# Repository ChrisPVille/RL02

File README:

Folder list:
board          - KiCad project, schematics and gerbers for board
FPGA           - Xilinx ISE Project
uC             - TI CCS project and C sources for micro-controller
Reference Docs - Supporting documentation for the RL02 and related

# RL02-USB Interface Project

## Overview

The aim of this project is to create an open-source interface between the DEC RL02 and a modern computer via USB.  

## Background

The RL02 hard drive was a mainstay of DEC's packaged computer systems in the late 1970s and 1980s.  Storing 10MB of data, these drives featured removable platters, 55ms average seek times, and ~250KBps effective linear throughput.  Combined with the modular design and longevity of the product line, there are still many functioning drives and many disk packs out there.

In addition to the historical aspects, many people still operate vintage computers for fun and profit.  Setting up operating system images and transferring files can be an ordeal when they can only be moved via serial or sneakernet from a very old system to a moderately old system to a modern system.  This interface serves to obviate the need for such setups by allowing the direct interface of the RL02 with a modern computer.

## The Interface

This new interface uses an FPGA to do all drive-facing tasks such as MFM data decoding, clock recovery, drive management, data buffering, etc.  The FPGA communicates with a microcontroller, exposing its data and a command interface over SPI.  That microcontroller serves as the USB mass storage/bulk transport device for the attached PC.

### FPGA

TODO: Expand

### Microcontroller

TODO: Expand

### PCB

TODO: Expand

(C) 2015 Christopher Parish

This program is free software: you can redistribute it and/or modify
it under the terms of the GNU General Public License as published by
the Free Software Foundation, either version 3 of the License, or
(at your option) any later version.  This is subject to the
exceptions listed in the LICENSE_EXCEPTION file.

This program is distributed in the hope that it will be useful,
but WITHOUT ANY WARRANTY; without even the implied warranty of
MERCHANTABILITY or FITNESS FOR A PARTICULAR PURPOSE.  See the
GNU General Public License for more details.

You should have received a copy of the GNU General Public License
along with this program.  If not, see <http://www.gnu.org/licenses/>.

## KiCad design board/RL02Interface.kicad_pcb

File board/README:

This folder contains the KiCad (https://launchpad.net/kicad) project files, schematic symbols, and related footprints as well as generated schematics and gerber files.

I generally run the latest KiCad built from sources, so I may be using features that don't exist in the pre-built versions.

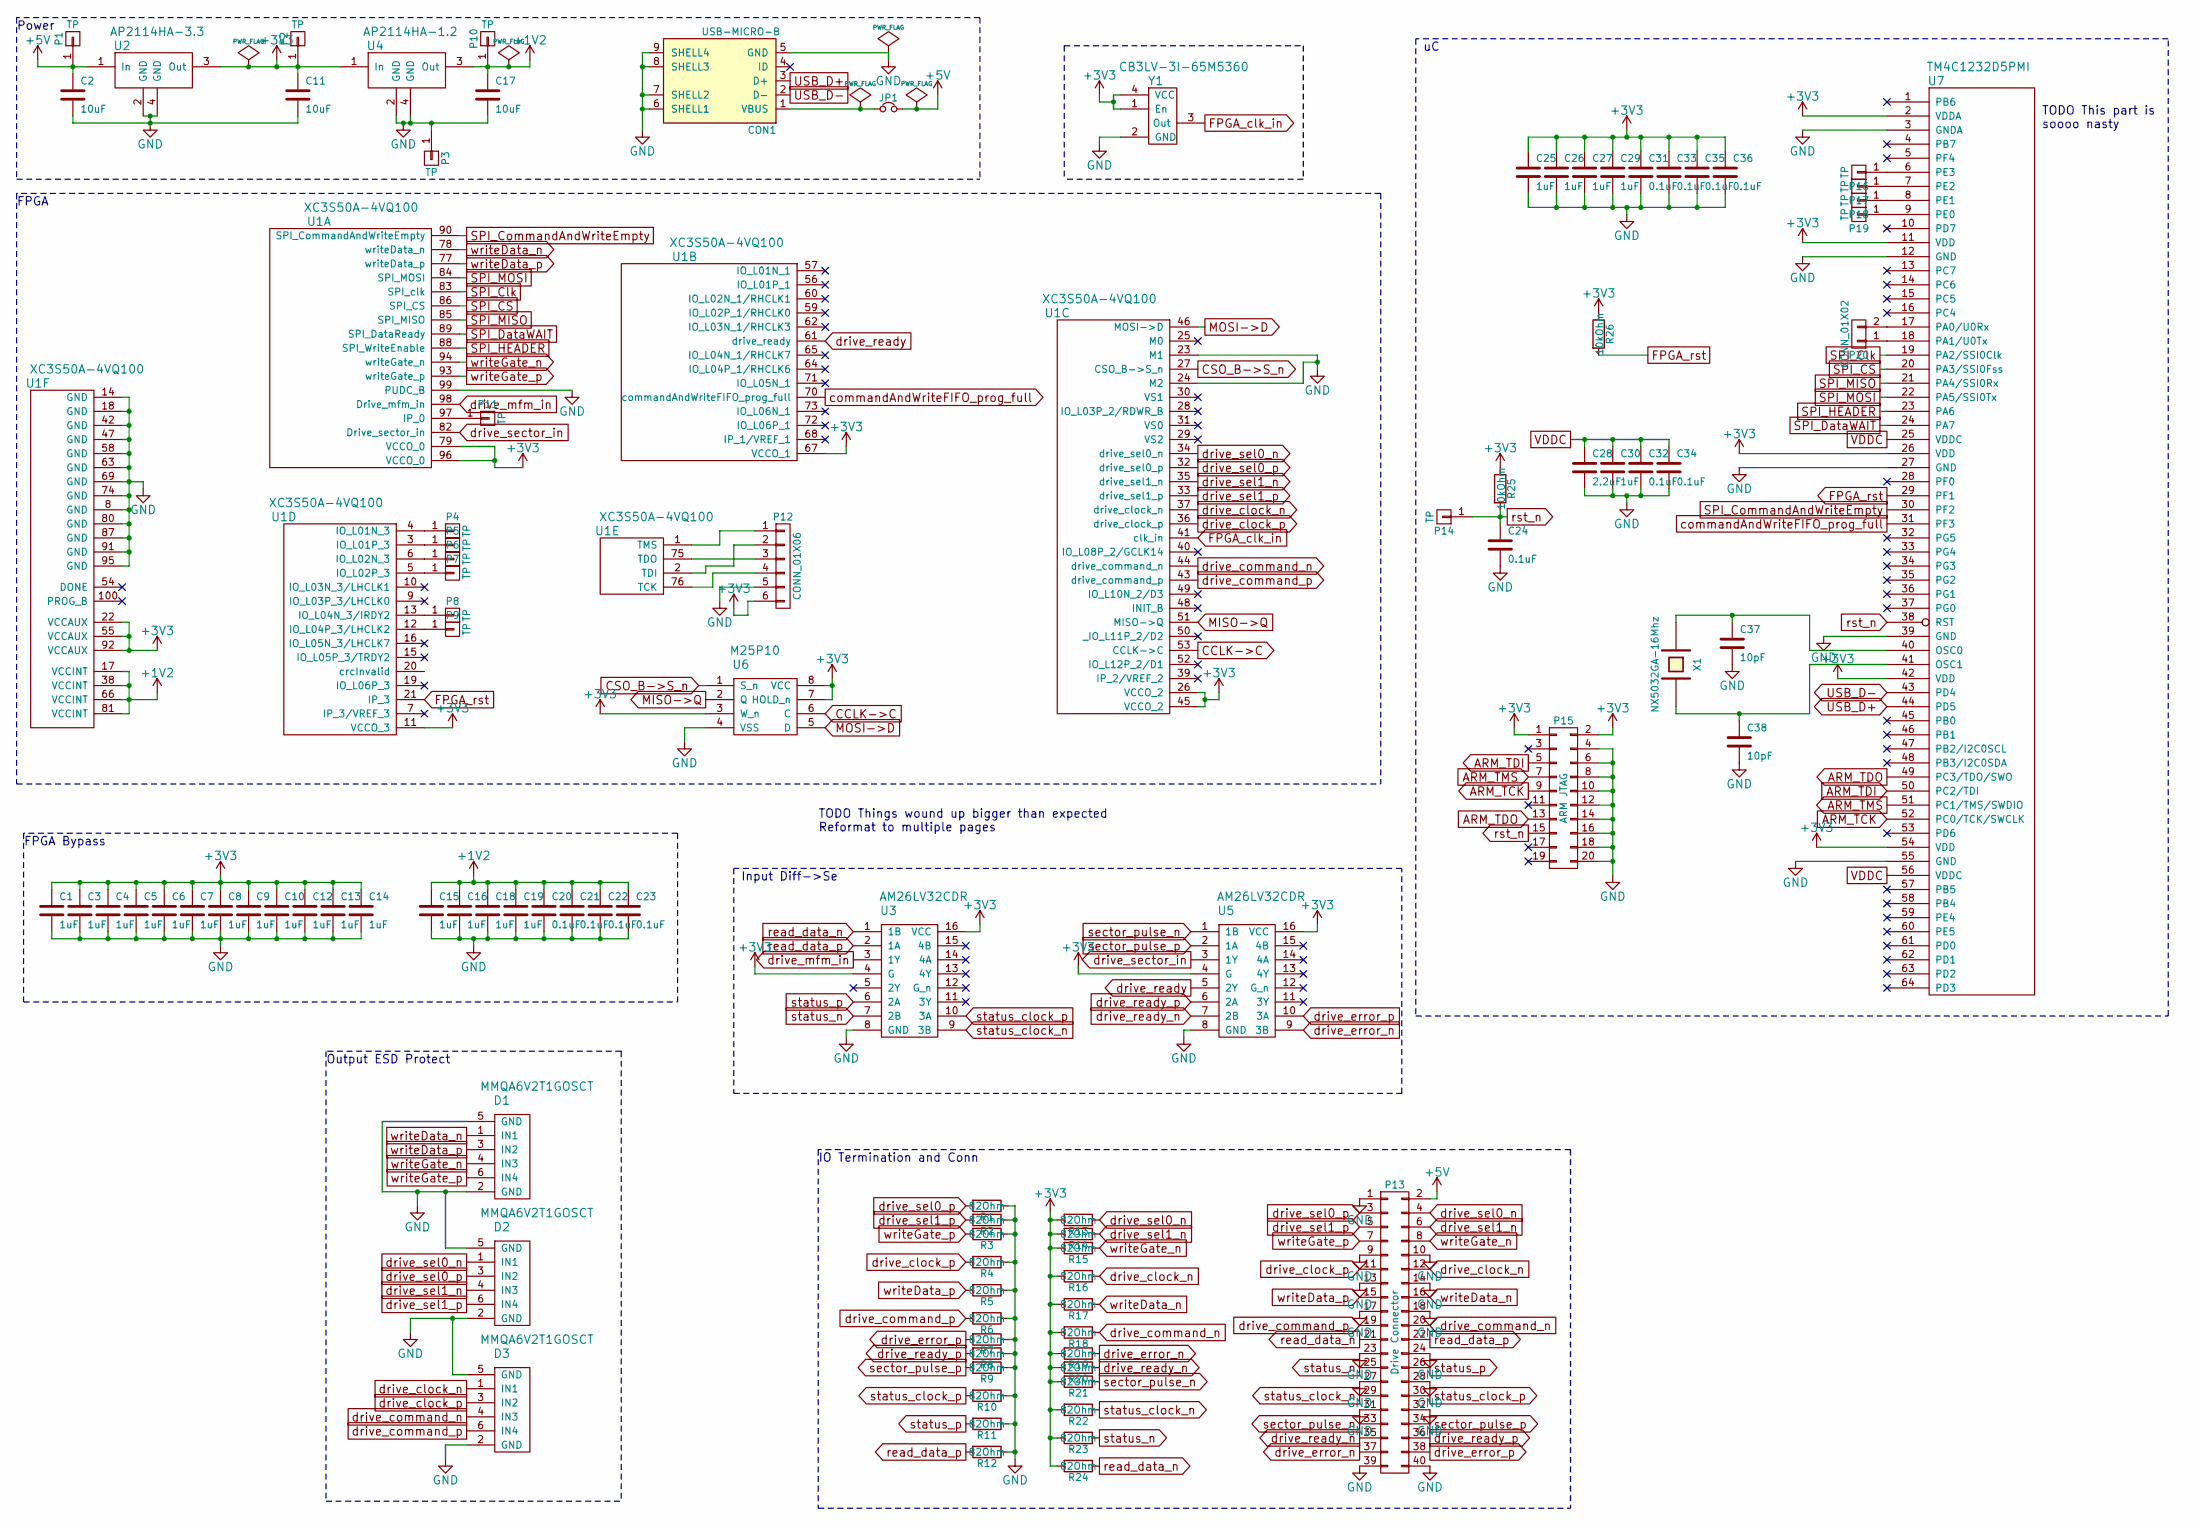
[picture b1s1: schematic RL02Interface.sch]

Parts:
C1, C3, C4, C5, C6, C7, C8, C9, C10, C12, C13, C14, C15, C16, C18, C19, C25, C26, C27, C29, C30: 1uF; C_0805
C2, C11, C17: 10uF; C_0805
C20, C21, C22, C23, C24, C31, C32, C33, C34, C35, C36: 0.1uF; C_0805
C28: 2.2uF; C_0805
C37, C38: 10pF; C_0805
CON1: USB-MICRO-B; MicroUSB-B
D1, D2, D3: MMQA6V2T1GOSCT; SOT-23-6
JP1: Jumper_NC_Small; Pin_Header_Straight_1x02
P1, P2, P3, P4, P5, P6, P7, P8, P9, P10, P11, P14, P16, P17, P18, P19: TP
P12: CONN_01X06; Pin_Header_Straight_1x06
P13: Drive Connector; Pin_Header_Straight_2x20
P15: ARM JTAG; Pin_Header_Straight_2x10
P20: CONN_01X02; Pin_Header_Straight_1x02
R1, R2, R3, R4, R5, R6, R7, R8, R9, R10, R11, R12, R13, R14, R15, R16, R17, R18, R19, R20, R21, R22, R23, R24: 82Ohm; R_0805
R25, R26: 10kOhm; R_0805
U1: XC3S50A-4VQ100; TQFP-100_14x14mm_Pitch0.5mm
U2: AP2114HA-3.3; SOT-223
U3, U5: AM26LV32CDR; SOIC-16_3.9x9.9mm_Pitch1.27mm
U4: AP2114HA-1.2; SOT-223
U6: M25P10; SOIC-8_3.9x4.9mm_Pitch1.27mm
U7: TM4C1232D5PMI; TQFP-64_10x10mm_Pitch0.5mm
X1: NX5032GA-16Mhz; C_1210_HandSoldering
Y1: CB3LV-3I-65M5360; CTSCrystal

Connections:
+1V2: C15.1, C16.1, C17.1, C18.1, C19.1, C20.1, C21.1, C22.1, C23.1, P10.1, U1.17 (VCCINT), U1.38 (VCCINT), U1.66 (VCCINT), U1.81 (VCCINT), U4.3 (Out); also elsewhere on the board
+3V3: C1.1, C3.1, C4.1, C5.1, C6.1, C7.1, C8.1, C9.1, C10.1, C11.1, C12.1, C13.1, C14.1, C25.1, C26.1, C27.1, C29.1, C31.1, C33.1, C35.1, C36.1, P2.1, P12.6, P15.1, P15.2, R13.2, R14.2, R15.2, R16.2, R17.2, R18.2, R19.2, R20.2, R21.2, R22.2, R23.2, R24.2, R25.1, R26.1, U1.11 (VCCO_3), U1.22 (VCCAUX), U1.26 (VCCO_2), U1.45 (VCCO_2), U1.55 (VCCAUX), U1.67 (VCCO_1), U1.79 (VCCO_0), U1.92 (VCCAUX), U1.96 (VCCO_0), U2.3 (Out), U3.4 (G), U3.16 (VCC), U4.1 (In), U5.4 (G), U5.16 (VCC), U6.3 (W_n), U6.7 (HOLD_n), U6.8 (VCC), U7.2 (VDDA), U7.11 (VDD), U7.26 (VDD), U7.42 (VDD), U7.54 (VDD), Y1.1 (En), Y1.4 (VCC); also elsewhere on the board
+5V: C2.1, JP1.2, P1.1, P13.2, U2.1 (In); also elsewhere on the board
ARM_TCK: P15.9, U7.52 (PC0/TCK/SWCLK)
ARM_TDI: P15.5, U7.50 (PC2/TDI)
ARM_TDO: P15.13, U7.49 (PC3/TDO/SWO)
ARM_TMS: P15.7, U7.51 (PC1/TMS/SWDIO)
CCLK->C: U1.53 (CCLK->C), U6.6 (C)
CSO_B->S_n: U1.27 (CSO_B->S_n), U6.1 (S_n)
FPGA_clk_in: U1.41 (clk_in), Y1.3 (Out)
FPGA_rst: R26.2, U1.21 (IP_3), U7.29 (PF1)
GND: C1.2, C2.2, C3.2, C4.2, C5.2, C6.2, C7.2, C8.2, C9.2, C10.2, C11.2, C12.2, C13.2, C14.2, C15.2, C16.2, C17.2, C18.2, C19.2, C20.2, C21.2, C22.2, C23.2, C24.2, C25.2, C26.2, C27.2, C28.2, C29.2, C30.2, C31.2, C32.2, C33.2, C34.2, C35.2, C36.2, C37.2, C38.2, CON1.5 (GND), CON1.6 (SHELL1), CON1.7 (SHELL2), CON1.8 (SHELL3), CON1.9 (SHELL4), CON1.PAD, D1.2 (GND), D1.5 (GND), D2.2 (GND), D2.5 (GND), D3.2 (GND), D3.5 (GND), P3.1, P12.5, P13.1, P13.9, P13.10, P13.13, P13.14, P13.17, P13.18, P13.23, P13.24, P13.27, P13.28, P13.31, P13.32, P13.39, P13.40, P15.4, P15.6, P15.8, P15.10, P15.12, P15.14, P15.16, P15.18, P15.20, R1.1, R2.1, R3.1, R4.1, R5.1, R6.1, R7.1, R8.1, R9.1, R10.1, R11.1, R12.1, U1.8 (GND), U1.14 (GND), U1.18 (GND), U1.23 (M1), U1.24 (M2), U1.42 (GND), U1.47 (GND), U1.58 (GND), U1.63 (GND), U1.69 (GND), U1.74 (GND), U1.80 (GND), U1.87 (GND), U1.91 (GND), U1.95 (GND), U1.99 (PUDC_B), U2.2 (GND), U2.4 (GND), U3.8 (GND), U4.2 (GND), U4.4 (GND), U5.8 (GND), U6.4 (VSS), U7.3 (GNDA), U7.12 (GND), U7.27 (GND), U7.39 (GND), U7.55 (GND), Y1.2 (GND); also elsewhere on the board
MISO->Q: U1.51 (MISO->Q), U6.2 (Q)
MOSI->D: U1.46 (MOSI->D), U6.5 (D)
unnamed: C37.1, U7.40 (OSC0), X1.1
unnamed: C38.1, U7.41 (OSC1), X1.2
unnamed: CON1.1 (VBUS), JP1.1
unnamed: P4.1, U1.4 (IO_L01N_3)
unnamed: P5.1, U1.3 (IO_L01P_3)
unnamed: P6.1, U1.6 (IO_L02N_3)
unnamed: P7.1, U1.5 (IO_L02P_3)
unnamed: P8.1, U1.13 (IO_L04N_3/IRDY2)
unnamed: P9.1, U1.12 (IO_L04P_3/LHCLK2)
unnamed: P11.1, U1.97 (IP_0)
unnamed: P12.1, U1.1 (TMS)
unnamed: P12.2, U1.2 (TDI)
unnamed: P12.3, U1.75 (TDO)
unnamed: P12.4, U1.76 (TCK)
unnamed: P16.1, U7.6 (PE3)
unnamed: P17.1, U7.7 (PE2)
unnamed: P18.1, U7.8 (PE1)
unnamed: P19.1, U7.9 (PE0)
unnamed: P20.1, U7.18 (PA1/U0Tx)
unnamed: P20.2, U7.17 (PA0/U0Rx)
SPI_CS: U1.86 (SPI_CS), U7.20 (PA3/SSI0Fss)
SPI_Clk: U1.83 (SPI_clk), U7.19 (PA2/SSI0Clk)
SPI_CommandAndWriteEmpty: U1.90 (SPI_CommandAndWriteEmpty), U7.30 (PF2)
SPI_DataWAIT: U1.89 (SPI_DataReady), U7.24 (PA7)
SPI_HEADER: U1.88 (SPI_WriteEnable), U7.23 (PA6)
SPI_MISO: U1.85 (SPI_MISO), U7.21 (PA4/SSI0Rx)
SPI_MOSI: U1.84 (SPI_MOSI), U7.22 (PA5/SSI0Tx)
USB_D+: CON1.3 (D+), U7.44 (PD5)
USB_D-: CON1.2 (D-), U7.43 (PD4)
VDDC: C28.1, C30.1, C32.1, C34.1, U7.25 (VDDC), U7.56 (VDDC)
commandAndWriteFIFO_prog_full: U1.70 (commandAndWriteFIFO_prog_full), U7.31 (PF3)
drive_clock_n: D3.1 (IN1), P13.12, R16.1, U1.37 (drive_clock_n)
drive_clock_p: D3.3 (IN2), P13.11, R4.2, U1.36 (drive_clock_p)
drive_command_n: D3.4 (IN3), P13.20, R18.1, U1.44 (drive_command_n)
drive_command_p: D3.6 (IN4), P13.19, R6.2, U1.43 (drive_command_p)
drive_error_n: P13.37, R19.1, U5.9 (3B)
drive_error_p: P13.38, R7.2, U5.10 (3A)
drive_mfm_in: U1.98 (Drive_mfm_in), U3.3 (1Y)
drive_ready: U1.61 (drive_ready), U5.5 (2Y)
drive_ready_n: P13.35, R20.1, U5.7 (2B)
drive_ready_p: P13.36, R8.2, U5.6 (2A)
drive_sector_in: U1.82 (Drive_sector_in), U5.3 (1Y)
drive_sel0_n: D2.1 (IN1), P13.4, R13.1, U1.34 (drive_sel0_n)
drive_sel0_p: D2.3 (IN2), P13.3, R1.2, U1.32 (drive_sel0_p)
drive_sel1_n: D2.4 (IN3), P13.6, R14.1, U1.35 (drive_sel1_n)
drive_sel1_p: D2.6 (IN4), P13.5, R2.2, U1.33 (drive_sel1_p)
read_data_n: P13.21, R24.1, U3.1 (1B)
read_data_p: P13.22, R12.2, U3.2 (1A)
rst_n: C24.1, P14.1, P15.15, R25.2, U7.38 (RST); also elsewhere on the board
sector_pulse_n: P13.33, R21.1, U5.1 (1B)
sector_pulse_p: P13.34, R9.2, U5.2 (1A)
status_clock_n: P13.29, R22.1, U3.9 (3B)
status_clock_p: P13.30, R10.2, U3.10 (3A)
status_n: P13.25, R23.1, U3.7 (2B)
status_p: P13.26, R11.2, U3.6 (2A)
writeData_n: D1.1 (IN1), P13.16, R17.1, U1.78 (writeData_n)
writeData_p: D1.3 (IN2), P13.15, R5.2, U1.77 (writeData_p)
writeGate_n: D1.4 (IN3), P13.8, R15.1, U1.94 (writeGate_n)
writeGate_p: D1.6 (IN4), P13.7, R3.2, U1.93 (writeGate_p)

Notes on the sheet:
TODO This part is soooo nasty
TODO Things wound up bigger than expected Reformat to multiple pages
FPGA
Power
FPGA Bypass
Output ESD Protect
IO Termination and Conn
Input Diff->Se

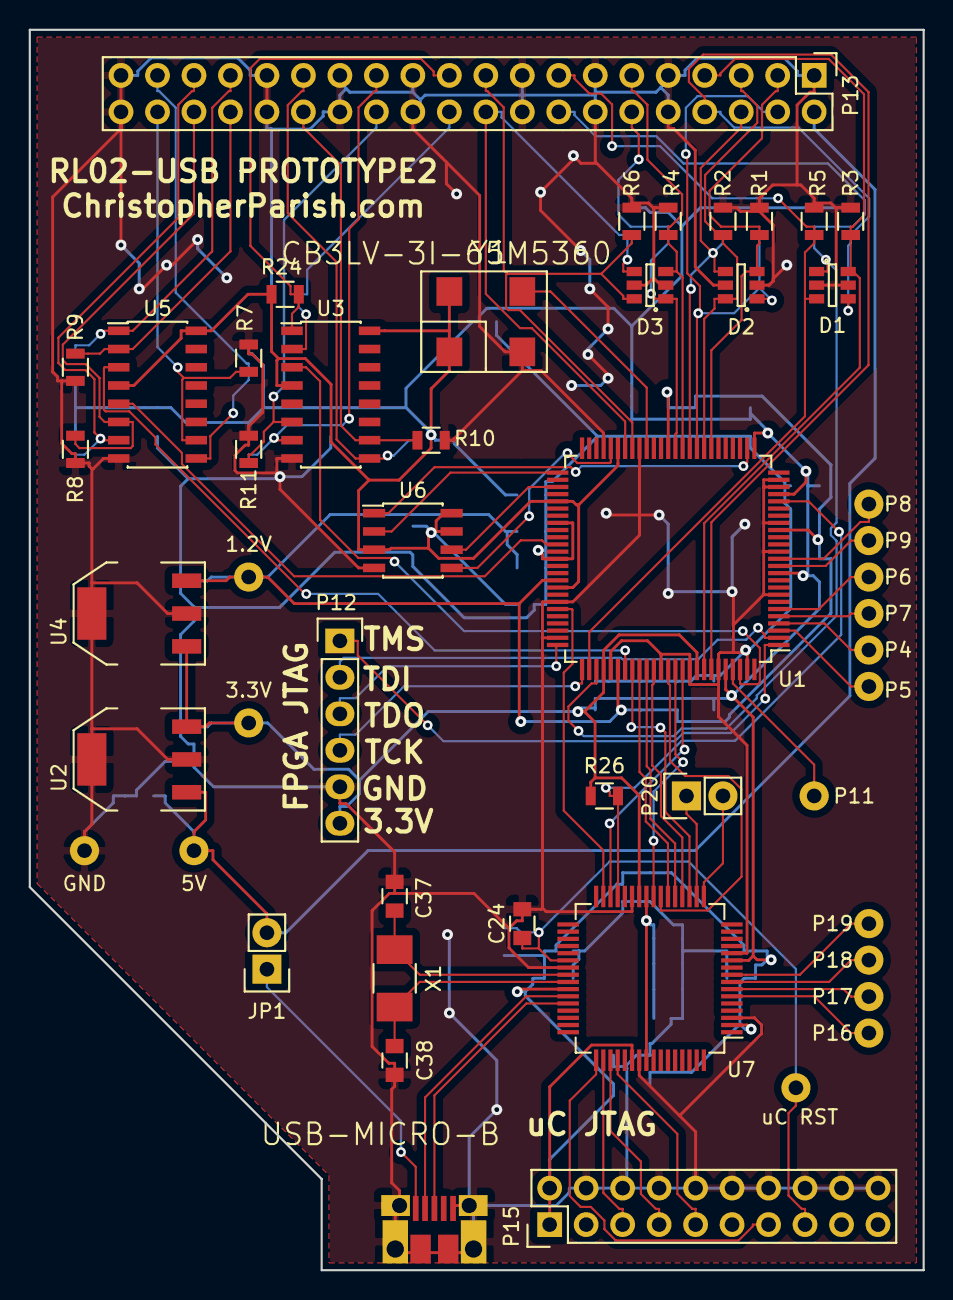
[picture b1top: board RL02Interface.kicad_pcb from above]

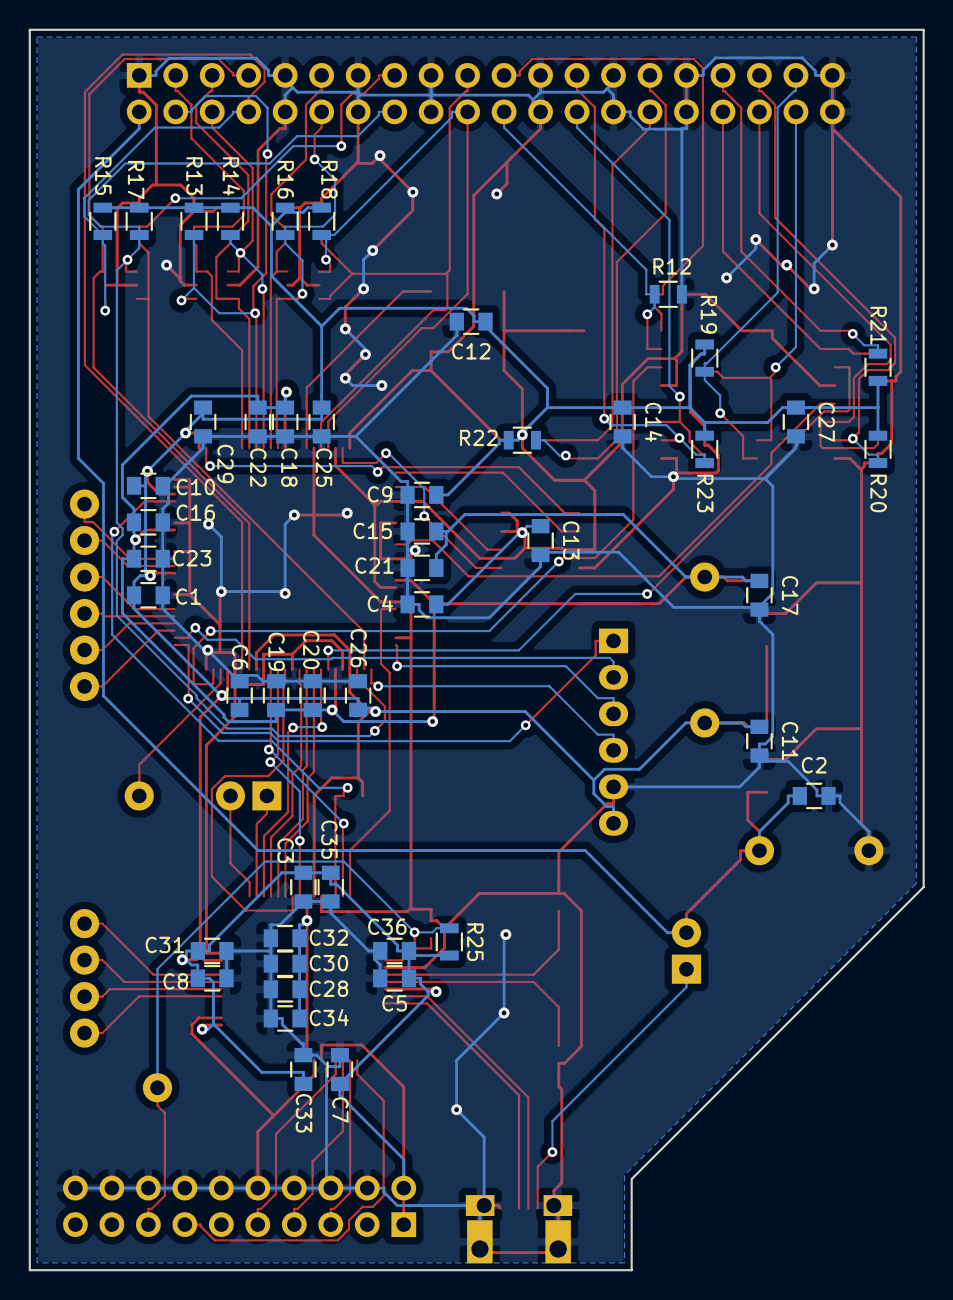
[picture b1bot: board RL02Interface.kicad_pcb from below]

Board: 2 copper layers, 62.2 x 86.4 mm, 98 parts (48 on the bottom side), 73 nets.

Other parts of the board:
1.2V, 3.3V, 5V: TP
GND: TP
uC RST: TP

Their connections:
+1V2: 1.2V.1; also elsewhere on the board
+3V3: 3.3V.1; also elsewhere on the board
+5V: 5V.1; also elsewhere on the board
GND: GND.1; also elsewhere on the board
rst_n: uC RST.1; also elsewhere on the board

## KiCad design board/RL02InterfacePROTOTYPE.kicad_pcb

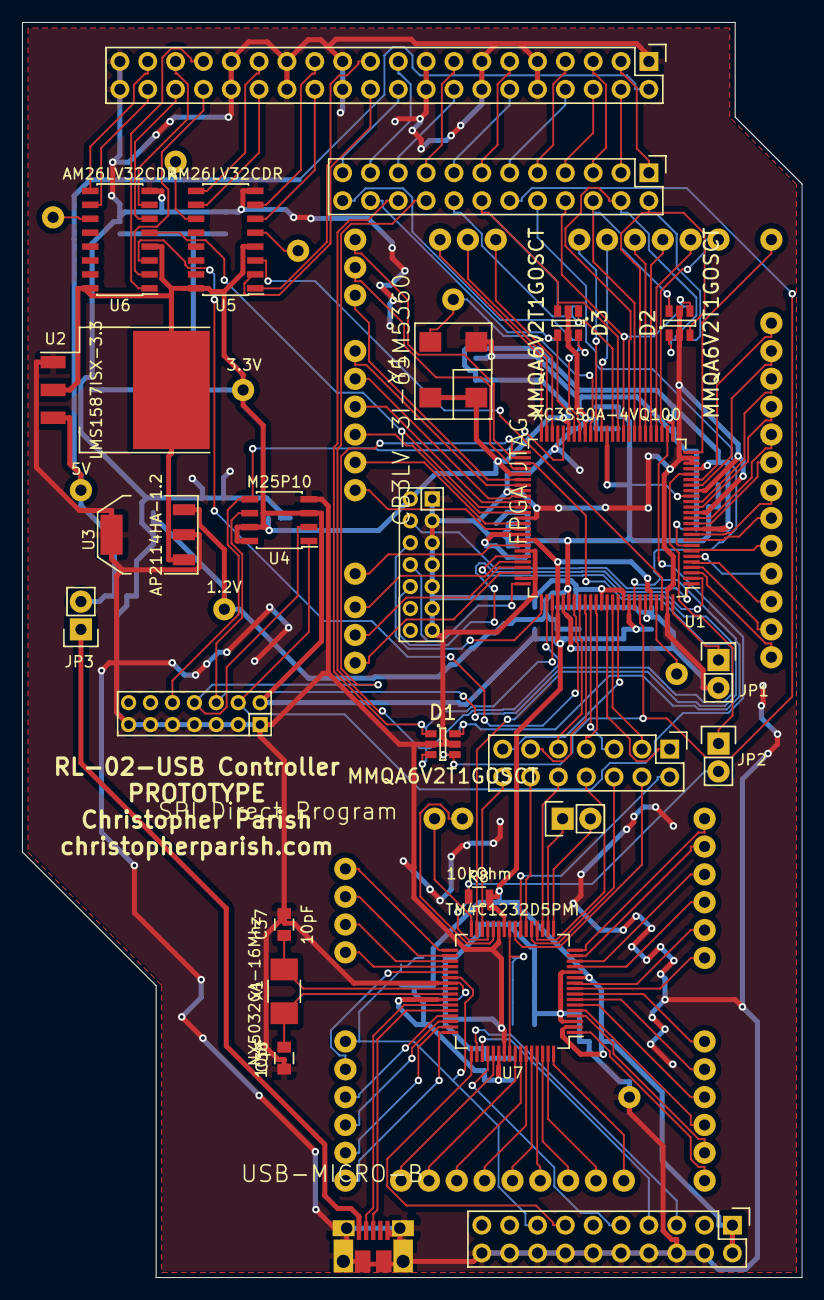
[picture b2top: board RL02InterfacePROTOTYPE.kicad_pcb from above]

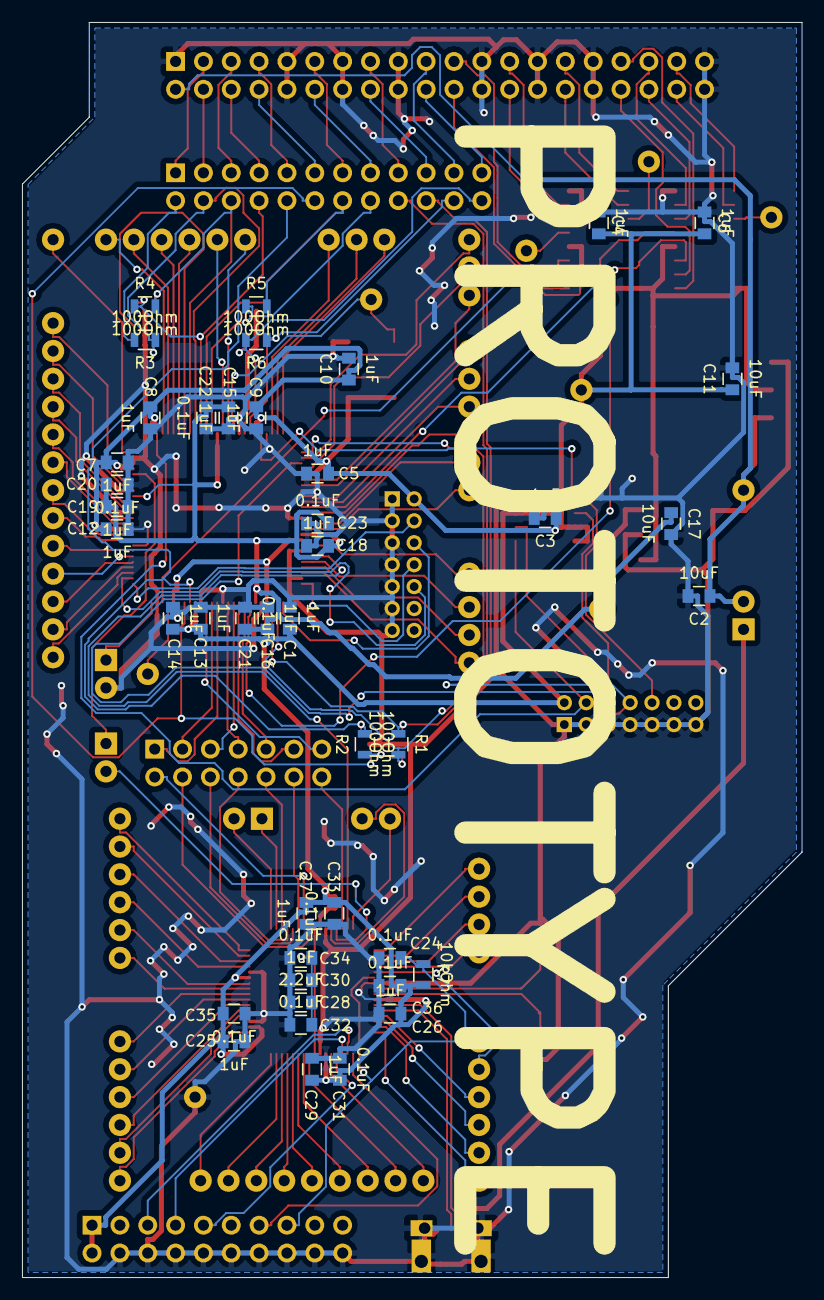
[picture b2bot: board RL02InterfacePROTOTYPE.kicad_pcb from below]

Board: 2 copper layers, 71.1 x 114.5 mm, 147 parts (43 on the bottom side), 155 nets.

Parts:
1.2V, 3.3V, 5V: TP
C1, C3, C4, C5, C6, C7, C8, C9, C10, C12, C13, C14, C15, C16, C18, C19, C25, C26, C27, C29, C30: 1uF; C_0805
C2, C11, C17: 10uF; C_0805
C20, C21, C22, C23, C24, C31, C32, C33, C34, C35, C36: 0.1uF; C_0805
C28: 2.2uF; C_0805
C37, C38: 10pF; C_0805
CON1: USB-MICRO-B; MicroUSB-B
D1, D2, D3: MMQA6V2T1GOSCT; SOT-23-6
JP1: SPI_PROGRAM; Pin_Header_Straight_1x02
JP2, JP3: JUMPER; Pin_Header_Straight_1x02
P2, P4, P5, P6, P7, P8, P9, P10, P11, P12, P13, P14, P15, P16, P17, P19, P23, P24, P25, P26, P27, P28, P29, P30, P31, P32, P33, P34, P35, P36, P37, P38, P39, P40, P41, P42, P43, P44, P45, P46, P47, P50, P52, P53, P54, P55, P56, P57, P58, P59, P60, P61, P62, P63, P65, P66, P67, P68, P69, P70, P71, P72, P73, P74, P75, P76, P77, P78, P79, P80, P81, P82, P83, P84, P85: TP
P20: SPI Debug; Pin_Header_Straight_2x07
P21: FPGA JTAG; 2x7_2.00mm_header
P22: SPI Direct Program; 2x7_2.00mm_header
P48: Data To Drive Disconnect; Pin_Header_Straight_2x12
P49: Drive Connector; Pin_Header_Straight_2x20
P51: ARM JTAG; Pin_Header_Straight_2x10
P64: CONN_01X02; Pin_Header_Straight_1x02
R1, R2, R3, R4, R5, R6: 100Ohm; R_0805
R7, R8: 10kOhm; R_0805
U1: XC3S50A-4VQ100; TQFP-100_14x14mm_Pitch0.5mm
U2: LMS1587ISX-3.3; TO-263
U3: AP2114HA-1.2; SOT-223
U4: M25P10; SOIC-8_3.9x4.9mm_Pitch1.27mm
U5, U6: AM26LV32CDR; SOIC-16_3.9x9.9mm_Pitch1.27mm
U7: TM4C1232D5PMI; TQFP-64_10x10mm_Pitch0.5mm
X1: NX5032GA-16Mhz; C_1210_HandSoldering
Y1: CB3LV-3I-65M5360; CTSCrystal

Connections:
+1V2: 1.2V.1, C15.1, C16.1, C17.1, C18.1, C19.1, C20.1, C21.1, C22.1, C23.1, U1.17, U1.38, U1.66, U1.81, U3.3
+3V3: 3.3V.1, C1.1, C3.1, C4.1, C5.1, C6.1, C7.1, C8.1, C9.1, C10.1, C11.1, C12.1, C13.1, C14.1, C25.1, C26.1, C27.1, C29.1, C31.1, C33.1, C35.1, C36.1, P21.2, P22.2, P51.1, P51.2, R7.1, R8.1, U1.11, U1.22, U1.26, U1.45, U1.55, U1.67, U1.79, U1.92, U1.96, U2.2, U2.PAD, U3.1, U4.3, U4.7, U4.8, U5.4, U5.16, U6.4, U6.16, U7.2, U7.11, U7.26, U7.42, U7.54, Y1.1, Y1.4
+5V: 5V.1, C2.1, JP3.2, P49.2, U2.3
ARM_TCK: P51.9, U7.52
ARM_TDI: P51.5, U7.50
ARM_TDO: P51.13, U7.49
ARM_TMS: P51.7, U7.51
CCLK->C: P22.6, U1.53, U4.6
CSO_B->S_n: P22.4, U1.27, U4.1
FPGA_clk_in: P66.1, U1.41, Y1.3
FPGA_rst: JP2.2, R8.2, U7.29
GND: C1.2, C2.2, C3.2, C4.2, C5.2, C6.2, C7.2, C8.2, C9.2, C10.2, C11.2, C12.2, C13.2, C14.2, C15.2, C16.2, C17.2, C18.2, C19.2, C20.2, C21.2, C22.2, C23.2, C24.2, C25.2, C26.2, C27.2, C28.2, C29.2, C30.2, C31.2, C32.2, C33.2, C34.2, C35.2, C36.2, C37.2, C38.2, CON1.5, CON1.PAD, D1.2, D1.5, D2.2, D2.5, D3.2, D3.5, JP1.2, P4.1, P21.1, P21.3, P21.5, P21.7, P21.9, P21.11, P21.13, P22.1, P22.3, P22.5, P22.7, P22.9, P22.11, P22.13, P49.1, P49.9, P49.10, P49.13, P49.14, P49.17, P49.18, P49.23, P49.24, P49.27, P49.28, P49.31, P49.32, P49.39, P49.40, P51.4, P51.6, P51.8, P51.10, P51.12, P51.14, P51.16, P51.18, P51.20, U1.8, U1.14, U1.18, U1.23, U1.24, U1.42, U1.47, U1.58, U1.63, U1.69, U1.74, U1.80, U1.87, U1.91, U1.95, U1.99, U2.1, U3.2, U3.4, U4.4, U5.8, U6.8, U7.3, U7.12, U7.27, U7.39, U7.55, Y1.2
MISO->Q: P22.8, U1.51, U4.2
MOSI->D: P22.10, U1.46, U4.5
unnamed: C37.1, U7.40, X1.1
unnamed: C38.1, U7.41, X1.2
unnamed: CON1.1, JP3.1
unnamed: JP1.1, U1.100
unnamed: JP2.1, U1.21
unnamed: P2.1, U1.54
unnamed: P5.1, U1.4
unnamed: P6.1, U1.3
unnamed: P7.1, U1.6
unnamed: P8.1, U1.5
unnamed: P9.1, U1.10
unnamed: P10.1, U1.9
unnamed: P11.1, U1.13
unnamed: P12.1, U1.12
unnamed: P13.1, U1.16
unnamed: P14.1, U1.15
unnamed: P15.1, U1.20
unnamed: P16.1, U1.19
unnamed: P17.1, U1.7
unnamed: P19.1, U1.97
unnamed: P20.1, U1.88
unnamed: P20.3, U1.89
unnamed: P20.5, U1.85
unnamed: P20.7, U1.86
unnamed: P20.9, U1.83
unnamed: P20.11, U1.84
unnamed: P20.13, U1.90
unnamed: P21.4, U1.1
unnamed: P21.6, U1.76
unnamed: P21.8, U1.75
unnamed: P21.10, U1.2
unnamed: P23.1, U1.57
unnamed: P24.1, U1.56
unnamed: P25.1, U1.60
unnamed: P26.1, U1.59
unnamed: P27.1, U1.62
unnamed: P28.1, U1.65
unnamed: P29.1, U1.64
unnamed: P30.1, U1.71
unnamed: P31.1, U1.73
unnamed: P32.1, U1.72
unnamed: P33.1, U1.68
unnamed: P34.1, U1.25
unnamed: P35.1, U1.30
unnamed: P36.1, U1.28
unnamed: P37.1, U1.31
unnamed: P38.1, U1.29
unnamed: P39.1, U1.40
unnamed: P40.1, U1.49
unnamed: P41.1, U1.48
unnamed: P42.1, U1.50
unnamed: P43.1, U1.52
unnamed: P44.1, U1.39
unnamed: P45.1, U5.5
unnamed: P46.1, U5.11
unnamed: P47.1, U6.11
unnamed: P48.1, P49.3
unnamed: P48.3, P49.4
unnamed: P48.5, P49.5
unnamed: P48.7, P49.6
unnamed: P48.9, P49.7
unnamed: P48.11, P49.8
unnamed: P48.13, P49.11
unnamed: P48.15, P49.12
unnamed: P48.17, P49.15
unnamed: P48.19, P49.16
unnamed: P48.21, P49.19
unnamed: P48.23, P49.20
unnamed: P52.1, U7.1
unnamed: P53.1, U7.4
unnamed: P54.1, U7.5
unnamed: P55.1, U7.6
unnamed: P56.1, U7.7
unnamed: P57.1, U7.8
unnamed: P58.1, U7.9
unnamed: P59.1, U7.10
unnamed: P60.1, U7.13
unnamed: P61.1, U7.14
unnamed: P62.1, U7.15
unnamed: P63.1, U7.16
unnamed: P64.1, U7.18
unnamed: P64.2, U7.17
unnamed: P65.1, U7.28
unnamed: P67.1, U7.32
unnamed: P68.1, U7.33
unnamed: P69.1, U7.34
unnamed: P70.1, U7.35
unnamed: P71.1, U7.36
unnamed: P72.1, U7.37
unnamed: P73.1, U7.45
unnamed: P74.1, U7.46
unnamed: P75.1, U7.47
unnamed: P76.1, U7.48
unnamed: P77.1, U7.53
unnamed: P78.1, U7.57
unnamed: P79.1, U7.58
unnamed: P80.1, U7.59
unnamed: P81.1, U7.60
unnamed: P82.1, U7.61
unnamed: P83.1, U7.62
unnamed: P84.1, U7.63
unnamed: P85.1, U7.64
SPI_CS: P20.8, U7.20
SPI_Clk: P20.10, U7.19
SPI_CommandAndWriteEmpty: P20.14, U7.30
SPI_DataReady: P20.4, U7.24
SPI_MISO: P20.6, U7.21
SPI_MOSI: P20.12, U7.22
SPI_WriteEnable: P20.2, U7.23
USB_D+: CON1.3, U7.44
USB_D-: CON1.2, U7.43
VDDC: C28.1, C30.1, C32.1, C34.1, U7.25, U7.56
commandAndWriteFIFO_prog_full: U1.70, U7.31
drive_clock_n: D3.1, P48.16, R5.1, U1.37
drive_clock_p: D3.3, P48.14, R5.2, U1.36
drive_command_n: D3.4, P48.22, R6.1, U1.44
drive_command_p: D3.6, P48.24, R6.2, U1.43
drive_error_n: P49.37, U6.9
drive_error_p: P49.38, U6.10
drive_mfm_in: U1.98, U5.3
drive_ready: U1.61, U6.5
drive_ready_n: P49.35, U6.7
drive_ready_p: P49.36, U6.6
drive_sector_in: U1.82, U6.3
drive_sel0_n: D2.1, P48.4, R3.1, U1.34
drive_sel0_p: D2.3, P48.2, R3.2, U1.32
drive_sel1_n: D2.4, P48.8, R4.1, U1.35
drive_sel1_p: D2.6, P48.6, R4.2, U1.33
read_data_n: P49.21, U5.1
read_data_p: P49.22, U5.2
rst_n: C24.1, P50.1, P51.15, R7.2, U7.38
sector_pulse_n: P49.33, U6.1
sector_pulse_p: P49.34, U6.2
status_clock_n: P49.29, U5.9
status_clock_p: P49.30, U5.10
status_n: P49.25, U5.7
status_p: P49.26, U5.6
writeData_n: D1.1, P48.20, R1.1, U1.78
writeData_p: D1.3, P48.18, R1.2, U1.77
writeGate_n: D1.4, P48.12, R2.1, U1.94
writeGate_p: D1.6, P48.10, R2.2, U1.93

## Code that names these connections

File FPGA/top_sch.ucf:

//SPI Boot mode pins
CONFIG PROHIBIT = P23;
CONFIG PROHIBIT = P24;
CONFIG PROHIBIT = P25;

//SPI Variant Select Pins
CONFIG PROHIBIT = P29;
CONFIG PROHIBIT = P30;
CONFIG PROHIBIT = P31;

//PUDC_B Pull up config
CONFIG PROHIBIT = P99;

//MISO/DIN -> Q
CONFIG PROHIBIT = P51;
//CSO_B -> S_n
CONFIG PROHIBIT = P27;
//CCLK -> C
CONFIG PROHIBIT = P53;
//MOSI -> D
CONFIG PROHIBIT = P46;

//INIT_B Init done
CONFIG PROHIBIT = P48;


# Specifies the minimum (worst-case) Vccint voltage for improved timing analysis
VOLTAGE  = 1.18;

# Specifies the Vccaux voltage (Spartan-3A/6)
CONFIG VCCAUX  = 3.3;
			
NET "clk_in" TNM_NET = "clk_in";
TIMESPEC TS_clk_in = PERIOD "clk_in" 65.536 MHz HIGH 50 % INPUT_JITTER 3 ps;


NET "SPI_CommandAndWriteEmpty" LOC = P90;
NET "SPI_DataWAIT" LOC = P89;
NET "SPI_MOSI" LOC = P84;
NET "SPI_CurWordIsHeader" LOC = P88;
NET "SPI_MISO" LOC = P85;
NET "SPI_CS" LOC = P86;
NET "SPI_clk" LOC = P83;

#pin2ucf - Sun Mar 08 22:31:16 2015
#The following constraints were newly added
NET "writeData_n" LOC = P78;
NET "writeData_p" LOC = P77;
NET "drive_command_n" LOC = P44;
NET "writeGate_n" LOC = P94;
NET "writeGate_p" LOC = P93;
NET "drive_command_p" LOC = P43;
NET "drive_clock_n" LOC = P37;
NET "drive_clock_p" LOC = P36;
NET "Drive_sector_in" LOC = P82;
NET "clk_in" LOC = P41;
NET "crcInvalid" LOC = P20;
NET "drive_ready" LOC = P61;
NET "drive_sel0_n" LOC = P34;
NET "drive_sel0_p" LOC = P32;
NET "commandAndWriteFIFO_prog_full" LOC = P70;
NET "drive_sel1_n" LOC = P35;
NET "drive_sel1_p" LOC = P33;
NET "Drive_mfm_in" LOC = P98;
NET "rst_in" LOC = P21;


# PlanAhead Generated IO constraints 

NET "clk_in" IOSTANDARD = LVCMOS33;
NET "commandAndWriteFIFO_prog_full" IOSTANDARD = LVCMOS33;
NET "crcInvalid" IOSTANDARD = LVCMOS33;
NET "Drive_mfm_in" IOSTANDARD = LVCMOS33;
NET "drive_ready" IOSTANDARD = LVCMOS33;
NET "Drive_sector_in" IOSTANDARD = LVCMOS33;
NET "rst_in" IOSTANDARD = LVCMOS33;
NET "SPI_clk" IOSTANDARD = LVCMOS33;
NET "SPI_CommandAndWriteEmpty" IOSTANDARD = LVCMOS33;
NET "SPI_CS" IOSTANDARD = LVCMOS33;
NET "SPI_DataWAIT" IOSTANDARD = LVCMOS33;
NET "SPI_MISO" IOSTANDARD = LVCMOS33 | SLEW=FAST;
NET "SPI_MOSI" IOSTANDARD = LVCMOS33;
NET "SPI_CurWordIsHeader" IOSTANDARD = LVCMOS33;

NET "drive_clock_p" IOSTANDARD = LVCMOS33 | SLEW=FAST | DRIVE=16;

NET "drive_command_p" IOSTANDARD = LVCMOS33 | SLEW=FAST | DRIVE=16;
NET "drive_command_n" IOSTANDARD = LVCMOS33 | SLEW=FAST | DRIVE=16;
NET "drive_sel0_p" IOSTANDARD = LVCMOS33 | DRIVE=16;
NET "drive_sel1_p" IOSTANDARD = LVCMOS33 | DRIVE=16;
NET "writeData_p" IOSTANDARD = LVCMOS33 | SLEW=FAST | DRIVE=16;
NET "drive_clock_n" IOSTANDARD = LVCMOS33 | SLEW=FAST | DRIVE=16;

NET "drive_sel0_n" IOSTANDARD = LVCMOS33 | DRIVE=16;
NET "drive_sel1_n" IOSTANDARD = LVCMOS33 | DRIVE=16;
NET "writeData_n" IOSTANDARD = LVCMOS33 | SLEW=FAST | DRIVE=16;
NET "writeGate_p" IOSTANDARD = LVCMOS33 | SLEW=FAST | DRIVE=16;
NET "writeGate_n" IOSTANDARD = LVCMOS33 | SLEW=FAST | DRIVE=16;

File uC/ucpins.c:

//*****************************************************************************
// Copyright (c) 2014 Texas Instruments Incorporated.  All rights reserved.
// Software License Agreement
//
//   Redistribution and use in source and binary forms, with or without
//   modification, are permitted provided that the following conditions
//   are met:
//
//   Redistributions of source code must retain the above copyright
//   notice, this list of conditions and the following disclaimer.
//
//   Redistributions in binary form must reproduce the above copyright
//   notice, this list of conditions and the following disclaimer in the
//   documentation and/or other materials provided with the
//   distribution.
//
//   Neither the name of Texas Instruments Incorporated nor the names of
//   its contributors may be used to endorse or promote products derived
//   from this software without specific prior written permission.
//
// THIS SOFTWARE IS PROVIDED BY THE COPYRIGHT HOLDERS AND CONTRIBUTORS
// "AS IS" AND ANY EXPRESS OR IMPLIED WARRANTIES, INCLUDING, BUT NOT
// LIMITED TO, THE IMPLIED WARRANTIES OF MERCHANTABILITY AND FITNESS FOR
// A PARTICULAR PURPOSE ARE DISCLAIMED. IN NO EVENT SHALL THE COPYRIGHT
// OWNER OR CONTRIBUTORS BE LIABLE FOR ANY DIRECT, INDIRECT, INCIDENTAL,
// SPECIAL, EXEMPLARY, OR CONSEQUENTIAL DAMAGES (INCLUDING, BUT NOT
// LIMITED TO, PROCUREMENT OF SUBSTITUTE GOODS OR SERVICES; LOSS OF USE,
// DATA, OR PROFITS; OR BUSINESS INTERRUPTION) HOWEVER CAUSED AND ON ANY
// THEORY OF LIABILITY, WHETHER IN CONTRACT, STRICT LIABILITY, OR TORT
// (INCLUDING NEGLIGENCE OR OTHERWISE) ARISING IN ANY WAY OUT OF THE USE
// OF THIS SOFTWARE, EVEN IF ADVISED OF THE POSSIBILITY OF SUCH DAMAGE.
//
// This file was automatically generated by the Tiva C Series PinMux Utility
// Version: 1.0.4
//
//*****************************************************************************

#include <stdint.h>
#include <stdbool.h>
#include "ucpins.h"
#include "inc/hw_types.h"
#include "inc/hw_memmap.h"
#include "inc/hw_gpio.h"
#include "driverlib/sysctl.h"
#include "driverlib/pin_map.h"
#include "driverlib/rom_map.h"
#include "driverlib/gpio.h"

//*****************************************************************************
void
PortFunctionInit(void)
{
    //
    // Enable Peripheral Clocks
    //
    MAP_SysCtlPeripheralEnable(SYSCTL_PERIPH_SSI0);
    MAP_SysCtlPeripheralEnable(SYSCTL_PERIPH_UART0);
    MAP_SysCtlPeripheralEnable(SYSCTL_PERIPH_USB0);
    MAP_SysCtlPeripheralEnable(SYSCTL_PERIPH_GPIOA);
    MAP_SysCtlPeripheralEnable(SYSCTL_PERIPH_GPIOD);
    MAP_SysCtlPeripheralEnable(SYSCTL_PERIPH_GPIOF);

    //
    // Enable pin PA7 for GPIOInput
    //
    MAP_GPIOPinTypeGPIOInput(GPIO_PORTA_BASE, GPIO_PIN_7);

    //
    // Enable pin PA6 for GPIOInput - SPI Current Word is Header Word
    //
    MAP_GPIOPinTypeGPIOInput(GPIO_PORTA_BASE, GPIO_PIN_6);

    //
    // Enable pin PF2 for GPIOInput
    //
    MAP_GPIOPinTypeGPIOInput(GPIO_PORTF_BASE, GPIO_PIN_2);

    //
    // Enable pin PF3 for GPIOInput
    //
    MAP_GPIOPinTypeGPIOInput(GPIO_PORTF_BASE, GPIO_PIN_3);

    //
    // Enable pin PF1 for GPIOOutputOD
    //
    MAP_GPIOPinTypeGPIOOutputOD(GPIO_PORTF_BASE, GPIO_PIN_1);

    //
    // Enable pin PA5 for SSI0 SSI0TX
    //
    MAP_GPIOPinConfigure(GPIO_PA5_SSI0TX);
    MAP_GPIOPinTypeSSI(GPIO_PORTA_BASE, GPIO_PIN_5);

    //
    // Enable pin PA4 for SSI0 SSI0RX
    //
    MAP_GPIOPinConfigure(GPIO_PA4_SSI0RX);
    MAP_GPIOPinTypeSSI(GPIO_PORTA_BASE, GPIO_PIN_4);

    //
    // Enable pin PA2 for SSI0 SSI0CLK
    //
    MAP_GPIOPinConfigure(GPIO_PA2_SSI0CLK);
    MAP_GPIOPinTypeSSI(GPIO_PORTA_BASE, GPIO_PIN_2);

    //
    // Enable pin PA3 for SSI0 SSI0FSS
    //
    MAP_GPIOPinConfigure(GPIO_PA3_SSI0FSS);
    MAP_GPIOPinTypeSSI(GPIO_PORTA_BASE, GPIO_PIN_3);

    //
    // Enable pin PA0 for UART0 U0RX
    //
    MAP_GPIOPinConfigure(GPIO_PA0_U0RX);
    MAP_GPIOPinTypeUART(GPIO_PORTA_BASE, GPIO_PIN_0);

    //
    // Enable pin PA1 for UART0 U0TX
    //
    MAP_GPIOPinConfigure(GPIO_PA1_U0TX);
    MAP_GPIOPinTypeUART(GPIO_PORTA_BASE, GPIO_PIN_1);

    //
    // Enable pin PD4 for USB0 USB0DM
    //
    MAP_GPIOPinTypeUSBAnalog(GPIO_PORTD_BASE, GPIO_PIN_4);

    //
    // Enable pin PD5 for USB0 USB0DP
    //
    MAP_GPIOPinTypeUSBAnalog(GPIO_PORTD_BASE, GPIO_PIN_5);
}

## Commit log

2015-04-21 Added reference docs
2015-04-21 Updated License
2015-04-22 Added board files and updated readme
2015-04-22 Added FPGA Files
2015-04-22 Fixed tabs and documentation reference
2015-04-22 Added folder READMEs
2015-04-22 too many words
2015-04-23 Added most (but not all) of the uC sources. More to follow.
2015-04-23 freed sector buffer on close (to support multiple drives)
2015-04-23 Prettified the code
2015-04-23 Updated license info
2015-04-23 try to get github to not count the ipcores in the stats
2015-04-24 Updated README and incidental FPGA build files
2015-04-24 Renamed README so it will get markdown formatted
2015-04-24 Made LICENSE_EXCEPTION more generic
2015-04-24 looks like KiCad's PDF generation isn't so perfect. Here's a SVG of the schematics if nothing else.
2015-04-26 Added project files and almost all remaining C files
2015-04-26 Added vector table file
2015-04-26 Added remaining uC files
2015-04-26 Removed some generated files that crept in the repo
2015-04-26 Tested regenerated IP cores and fixed observed issues fresh installs will have
2015-04-27 Update .gitattributes
    GitHub is assuming my C files are C++
2015-04-27 Added BOM
2015-05-02 Removed some build logs
2015-05-04 First pass at write support
2015-05-04 removed binaries that crept into project
2015-05-04 Fixing up write support
2015-05-07 Added synchronizer on SPI clock
